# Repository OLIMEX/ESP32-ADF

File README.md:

# ESP32-ADF
ESP32 Audio Development Framework development board

[ESP32-ADF product page](https://www.olimex.com/Products/IoT/ESP32/ESP32-ADF/)

# ESP32-ADF board has these features:
- ESP32-WROVER-B module with 8MB PSRAM, 4MB Flash
- Stereo codec and Audio Amplifier 2x3W
- Stereo Microphones
- Audio out 3.5mm jack
- UEXT connector for sensors and LCDs
- Lipo battery charger
- USB connector and programmer
- Four touch buttons, 3 tactile buttons
- power supply Jack for +5V 1A

# License
- Hardware is with CERN OHL v1.2 license
- Software is with GPL3 license
- Documentation is with CC BY-SA 4.0 license

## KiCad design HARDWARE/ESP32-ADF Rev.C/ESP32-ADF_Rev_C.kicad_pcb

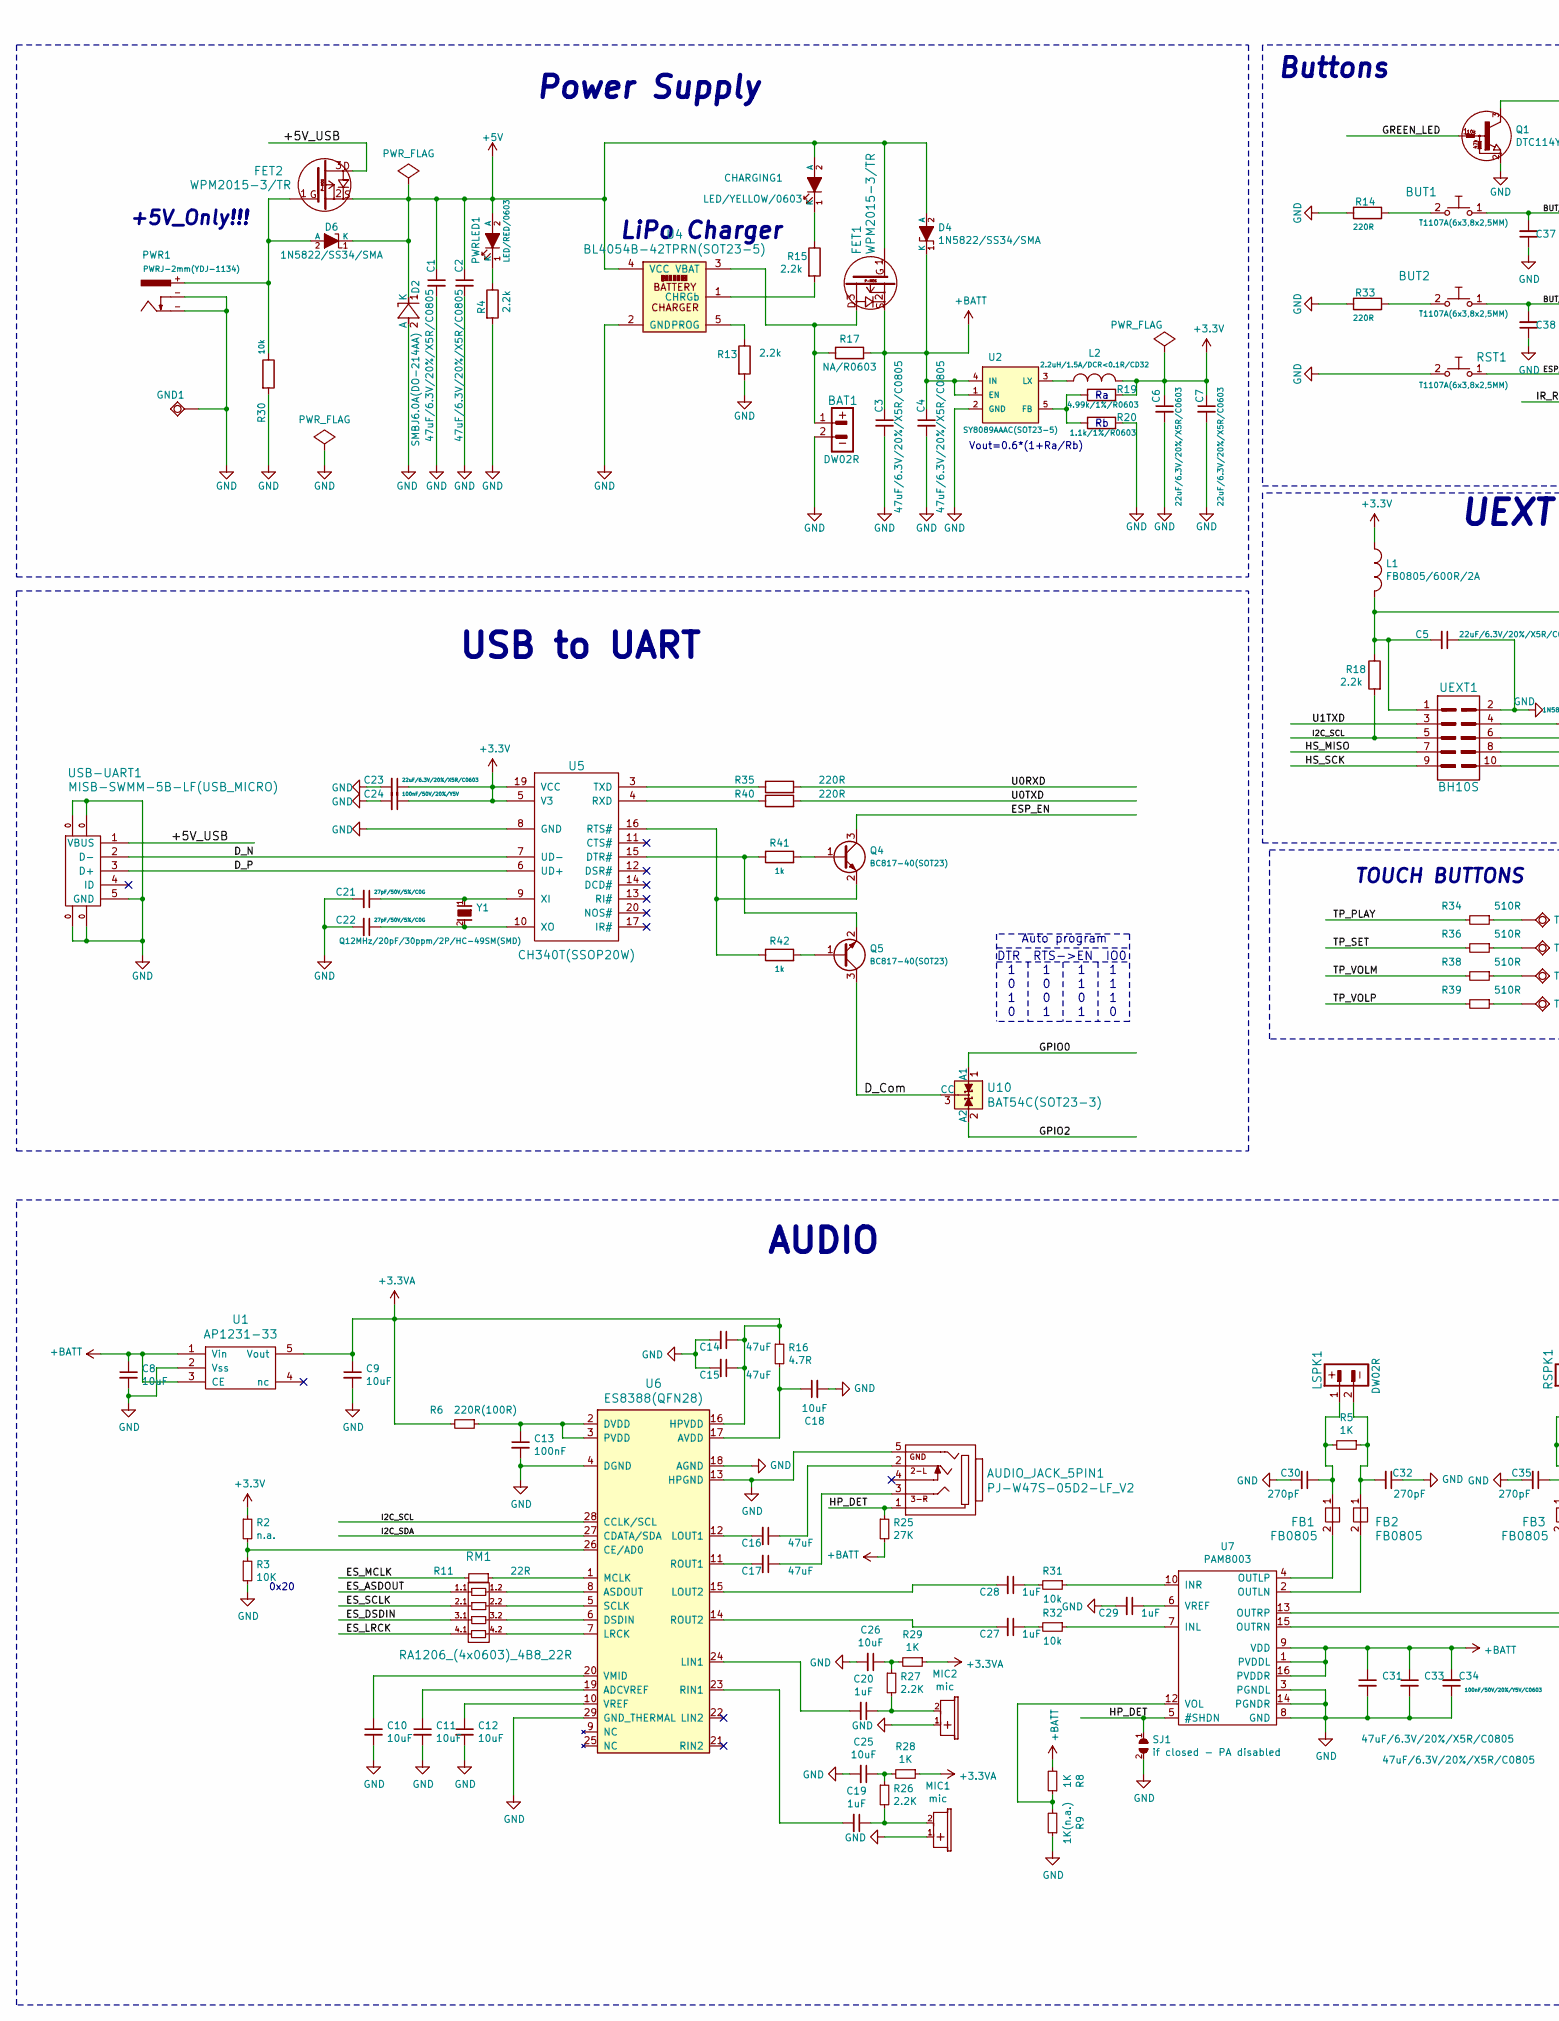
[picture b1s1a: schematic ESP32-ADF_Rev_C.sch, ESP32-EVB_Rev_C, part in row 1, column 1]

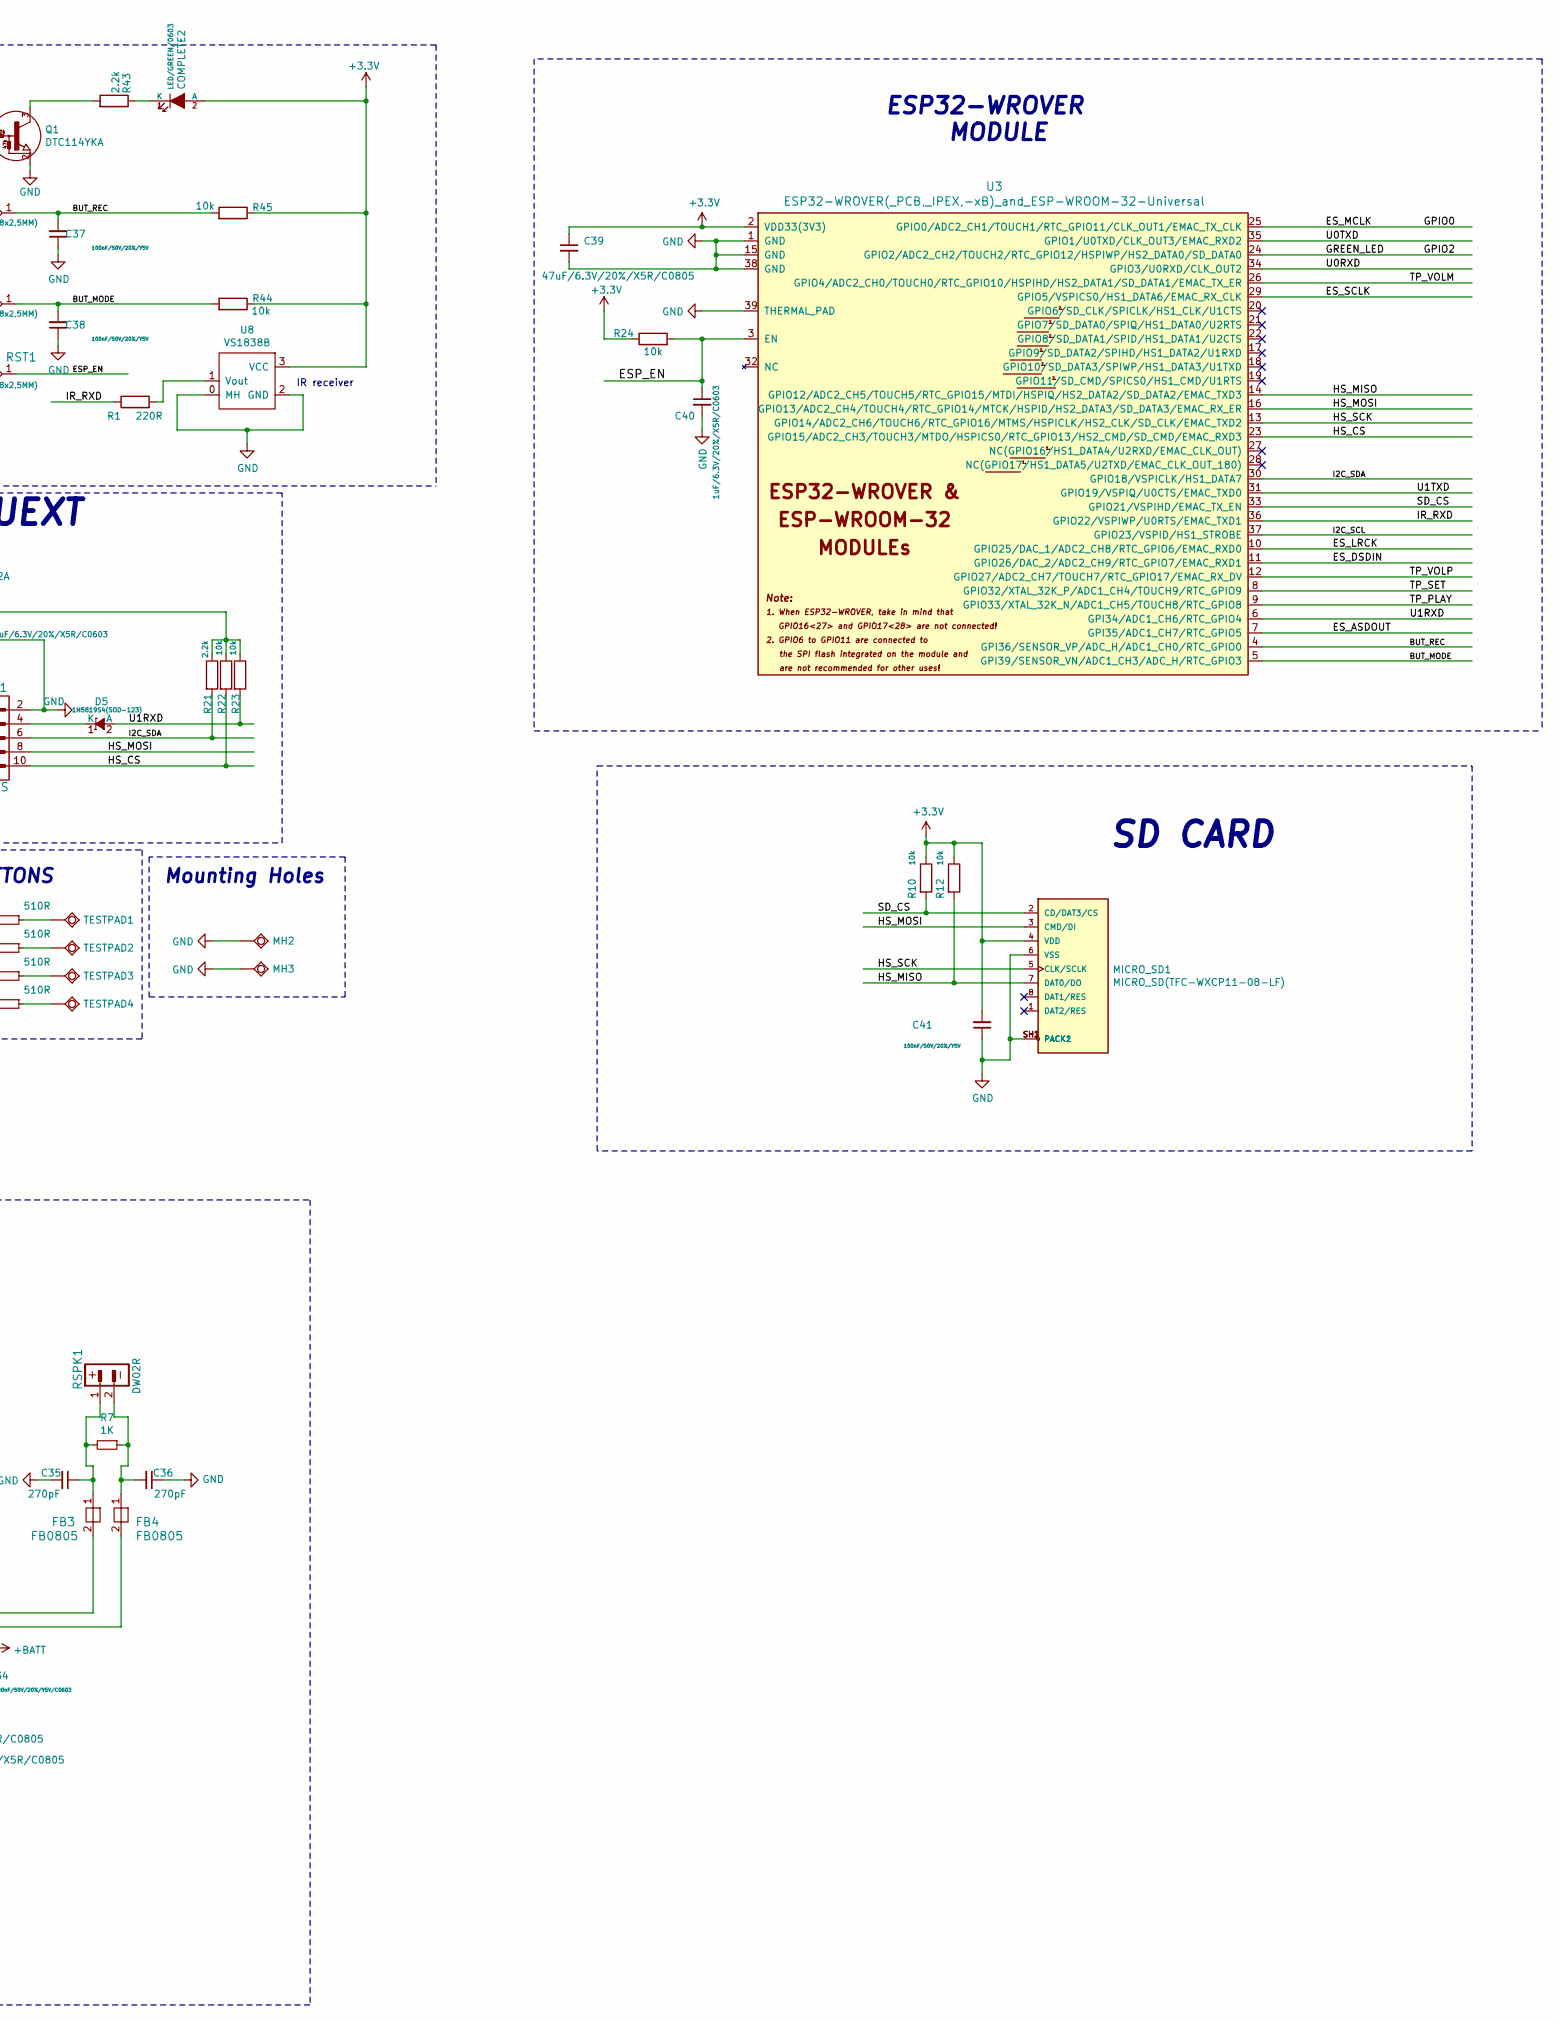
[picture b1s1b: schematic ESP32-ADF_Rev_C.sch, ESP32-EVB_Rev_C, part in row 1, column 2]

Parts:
AUDIO_JACK_5PIN1: PJ-W47S-05D2-LF_V2; PJ-W47S-05D2-LF_5PIN_V2
BAT1: DW02R; LIPO_BAT-CON2DW02R
BUT1, BUT2: T1107A(6x3,8x2,5MM)
C1, C2, C3, C4, C31, C33, C39: 47uF/6.3V/20%/X5R/C0805; C_0805_5MIL_DWS
C5, C6, C7, C23: 22uF/6.3V/20%/X5R/C0603; C_0603_5MIL_DWS
C8, C9, C10, C11, C12, C18, C25, C26: 10uF; C_0603_5MIL_DWS
C13: 100nF; C_0603_5MIL_DWS
C14, C15, C16, C17: 47uF; C_0805_5MIL_DWS
C19, C20, C27, C28, C29: 1uF; C_0603_5MIL_DWS
C21, C22: 27pF/50V/5%/C0G; C_0603_5MIL_DWS
C24: 100nF/50V/20%/Y5V; C_0603_5MIL_DWS
C30, C32, C35, C36: 270pF; C_0402_5MIL_DWS
C34: 100nF/50V/20%/Y5V/C0603; C_0402_5MIL_DWS
C37, C38, C41: 100nF/50V/20%/Y5V; C_0402_5MIL_DWS
C40: 1uF/6.3V/20%/X5R/C0603; C_0603_5MIL_DWS
CHARGING1: LED/YELLOW/0603; LED_0603_KA
COMPLETE2: LED/GREEN/0603; LED_0603_KA
D2: SMBJ6.0A(DO-214AA); DO214AA_1(K)-2(A)
D4, D6: 1N5822/SS34/SMA; SMA-KA
D5: 1N5819S4(SOD-123); SOD-123_1C-2A_KA
FB1, FB2, FB3, FB4: FB0805; L_0805_5MIL_DWS
FET1, FET2: WPM2015-3/TR; SOT23
GND1: TESTPAD; TESTPAD_40-ROUND
L1: FB0805/600R/2A; L_0805_5MIL_DWS
L2: 2.2uH/1.5A/DCR<0.1R/CD32; CD32
LSPK1: DW02R; LIPO_BAT-CON2DW02R
MH2, MH3: Mounting_hole_Shield_3.3mm
MIC1, MIC2: mic; MIC
MICRO_SD1: MICRO_SD(TFC-WXCP11-08-LF); TFC-WXCP11-08-LF
PWR1: PWRJ-2mm(YDJ-1134); PWRJ-2mm(YDJ-1136)
PWRLED1: LED/RED/0603; LED_0603_KA
Q1: DTC114YKA; SOT23
Q4, Q5: BC817-40(SOT23); SOT23
R1, R14, R33, R35, R40: 220R; R_0402_5MIL_DWS
R2: n.a.; R_0402_5MIL_DWS
R3: 10K; R_0402_5MIL_DWS
R4, R13, R15, R18, R21, R43: 2.2k; R_0402_5MIL_DWS
R5, R7, R8, R28, R29: 1K; R_0402_5MIL_DWS
R6: 220R(100R); R_0402_5MIL_DWS
R9: 1K(n.a.); R_0402_5MIL_DWS
R10, R12, R22, R23, R24, R30, R31, R32, R44, R45: 10k; R_0402_5MIL_DWS
R11: 22R; R_0402_5MIL_DWS
R16: 4.7R; R_0402_5MIL_DWS
R17: NA/R0603; R_0402_5MIL_DWS
R19: 4.99k/1%/R0603; R_0603_5MIL_DWS
R20: 1.1k/1%/R0603; R_0603_5MIL_DWS
R25: 27K; R_0402_5MIL_DWS
R26, R27: 2.2K; R_0402_5MIL_DWS
R34, R36, R38, R39: 510R; R_0402_5MIL_DWS
R41, R42: 1k; R_0402_5MIL_DWS
RM1: RA1206_(4x0603)_4B8_22R; RA1206_(4X0603)_4B8_mine_1.1
RSPK1: DW02R; LIPO_BAT-CON2DW02R
RST1: T1107A(6x3,8x2,5MM)
SJ1: if closed - PA disabled; SJ
TESTPAD1, TESTPAD2, TESTPAD3, TESTPAD4: TESTPAD; TP_SMD_10.00x5.00mm
U1: AP1231-33; SOT-23-5
U2: SY8089AAAC(SOT23-5); SOT-23-5
U3: ESP32-WROVER(_PCB,_IPEX,-xB)_and_ESP-WROOM-32-Uni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; ESP32-WROVER_MODULE_
U4: BL4054B-42TPRN(SOT23-5); SOT-23-5
U5: CH340T(SSOP20W); SSOP-20W
U6: ES8388(QFN28); QFN28_EP(29)_4.076x4.076x0.9mm_Pitch_0.45mm
U7: PAM8003; SO-16
U8: VS1838B; RPM7236-H8
U10: BAT54C(SOT23-3); SOT23
UEXT1: BH10S; GBH-254-SMT-10_Smaller
USB-UART1: MISB-SWMM-5B-LF(USB_MICRO); USB-MICRO_MISB-SWMM-5B_LF
Y1: Q12MHz/20pF/30ppm/2P/HC-49SM(SMD); TSX-3.2x2.5mm_GND(3)

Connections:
+3.3VA: C9.1, C14.1, C15.1, R6.2, R16.1, R28.1, R29.1, U1.5 (Vout), U6.16 (HPVDD)
+3V3: C6.1, C7.1, C23.1, C24.1, C39.1, C41.2, COMPLETE2.2 (A), L1.1, L2.2, MICRO_SD1.4 (VDD), R2.1, R10.1, R12.1, R19.2, R24.1, R44.1, R45.1, U3.2 (VDD33(3V3)), U5.5 (V3), U5.19 (VCC), U8.3 (VCC)
+5V: C1.1, C2.1, CHARGING1.2 (A), D2.1 (K), D4.2 (A), D6.1 (K), FET1.1, FET2.2, PWRLED1.2 (A), U4.4 (VCC)
+BATT: C3.1, C4.1, C8.1, C31.1, C33.1, C34.2, D4.1 (K), FET1.2, R8.2, R17.2, R25.2, U1.1 (Vin), U1.3 (CE), U2.1 (EN), U2.4 (IN), U7.1 (PVDDL), U7.9 (VDD), U7.16 (PVDDR)
/+5V_USB: FET2.3, USB-UART1.1 (VBUS)
/BUT_MODE: BUT2.1, C38.2, R44.2, U3.5 (GPI39/SENSOR_VN/ADC1_CH3/ADC_H/RTC_GPIO3)
/BUT_REC: BUT1.1, C37.2, R45.2, U3.4 (GPI36/SENSOR_VP/ADC_H/ADC1_CH0/RTC_GPIO0)
/D_Com: Q5.3 (C), U10.3 (CC)
/D_N: U5.7 (UD-), USB-UART1.2 (D-)
/D_P: U5.6 (UD+), USB-UART1.3 (D+)
/ESP_EN: C40.1, Q4.3 (C), R24.2, RST1.1, U3.3 (EN)
/ES_ASDOUT: RM1.1.1, U3.7 (GPI35/ADC1_CH7/RTC_GPIO5)
/ES_DSDIN: RM1.3.1, U3.11 (GPIO26/DAC_2/ADC2_CH9/RTC_GPIO7/EMAC_RX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)
/ES_LRCK: RM1.4.1, U3.10 (GPIO25/DAC_1/ADC2_CH8/RTC_GPIO6/EMAC_RX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)
/ES_MCLK: R11.2, U3.25 (GPIO0/ADC2_CH1/TOUCH1/RTC_GPIO11/CLK_OU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), U10.1 (A1)
/ES_SCLK: RM1.2.1, U3.29 (GPIO5/VSPICS0/HS1_DATA6/EMAC_RX_CLK)
/GPIO2: Q1.1 (B), U3.24 (GPIO2/ADC2_CH2/TOUCH2/RTC_GPIO12/HSPIWP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), U10.2 (A2)
/HP_DET: AUDIO_JACK_5PIN1.1, R25.1, SJ1.1, U7.5 (#SHDN)
/HS_CS: R22.2, U3.23 (GPIO15/ADC2_CH3/TOUCH3/MTDO/HSPICS0/RTC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), UEXT1.10
/HS_MISO: MICRO_SD1.7 (DAT0/DO), R12.2, U3.14 (GPIO12/ADC2_CH5/TOUCH5/RTC_GPIO15/MTDI/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), UEXT1.7
/HS_MOSI: MICRO_SD1.3 (CMD/DI), U3.16 (GPIO13/ADC2_CH4/TOUCH4/RTC_GPIO14/MTCK/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), UEXT1.8
/HS_SCK: MICRO_SD1.5 (CLK/SCLK), U3.13 (GPIO14/ADC2_CH6/TOUCH6/RTC_GPIO16/MTMS/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), UEXT1.9
/I2C_SCL: R18.2, U3.37 (GPIO23/VSPID/HS1_STROBE), U6.28 (CCLK/SCL), UEXT1.5
/I2C_SDA: R21.2, U3.30 (GPIO18/VSPICLK/HS1_DATA7), U6.27 (CDATA/SDA), UEXT1.6
/IR_RXD: R1.1, U3.36 (GPIO22/VSPIWP/U0RTS/EMAC_TXD1)
/SD_CS: MICRO_SD1.2 (CD/DAT3/CS), R10.2, U3.33 (GPIO21/VSPIHD/EMAC_TX_EN)
/TP_PLAY: R34.2, U3.9 (GPIO33/XTAL_32K_N/ADC1_CH5/TOUCH8/RTC_G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)
/TP_SET: R36.2, U3.8 (GPIO32/XTAL_32K_P/ADC1_CH4/TOUCH9/RTC_G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)
/TP_VOLM: R38.2, U3.26 (GPIO4/ADC2_CH0/TOUCH0/RTC_GPIO10/HSPIHD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)
/TP_VOLP: R39.2, U3.12 (GPIO27/ADC2_CH7/TOUCH7/RTC_GPIO17/EMAC_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)
/U0RXD: R35.2, U3.34 (GPIO3/U0RXD/CLK_OUT2)
/U0TXD: R40.2, U3.35 (GPIO1/U0TXD/CLK_OUT3/EMAC_RXD2)
/U1RXD: D5.2 (A), R23.2, U3.6 (GPI34/ADC1_CH6/RTC_GPIO4)
/U1TXD: U3.31 (GPIO19/VSPIQ/U0CTS/EMAC_TXD0), UEXT1.3
GND: AUDIO_JACK_5PIN1.5, BAT1.2, C1.2, C2.2, C3.2, C4.2, C5.1, C6.2, C7.2, C8.2, C9.2, C10.2, C11.2, C12.2, C13.2, C14.2, C15.2, C18.2, C21.2, C22.2, C23.2, C24.2, C25.2, C26.2, C29.2, C30.2, C31.2, C32.1, C33.2, C34.1, C35.2, C36.1, C37.1, C38.1, C39.2, C40.2, C41.1, D2.2 (A), GND1.1, MH2.GND1, MH3.GND1, MIC1.1 (PLUS), MIC2.1 (PLUS), MICRO_SD1.6 (VSS), MICRO_SD1.SH1 (PACK1), MICRO_SD1.SH2 (PACK2), PWR1.-, Q1.2 (E), R3.2, R4.2, R9.1, R13.2, R14.2, R20.2, R30.2, R33.2, RST1.2, SJ1.2, U1.2 (Vss), U2.2 (GND), U3.1 (GND), U3.15 (GND), U3.38 (GND), U3.39 (THERMAL_PAD), U4.2 (GND), U5.8 (GND), U6.4 (DGND), U6.13 (HPGND), U6.18 (AGND), U6.29 (GND_THERMAL), U7.3 (PGNDL), U7.8 (GND), U7.14 (PGNDR), U8.0 (MH), U8.2 (GND), UEXT1.2, USB-UART1.0, USB-UART1.5 (GND); also elsewhere on the board
unnamed: AUDIO_JACK_5PIN1.2, C16.1
unnamed: AUDIO_JACK_5PIN1.3, C17.1
unnamed: BAT1.1, FET1.3, R17.1, U4.3 (VBAT)
unnamed: BUT1.2, R14.1
unnamed: BUT2.2, R33.1
unnamed: C5.2, L1.2, R18.1, R21.1, R22.1, R23.1, UEXT1.1
unnamed: C10.1, U6.20 (VMID)
unnamed: C11.1, U6.19 (ADCVREF)
unnamed: C12.1, U6.10 (VREF)
unnamed: C13.1, R6.1, U6.2 (DVDD), U6.3 (PVDD)
unnamed: C16.2, U6.12 (LOUT1)
unnamed: C17.2, U6.11 (ROUT1)
unnamed: C18.1, R16.2, U6.17 (AVDD)
unnamed: C19.1, MIC1.2 (MINUS), R26.2
unnamed: C19.2, U6.23 (RIN1)
unnamed: C20.1, MIC2.2 (MINUS), R27.2
unnamed: C20.2, U6.24 (LIN1)
unnamed: C21.1, U5.9 (XI), Y1.1
unnamed: C22.1, U5.10 (XO), Y1.2
unnamed: C25.1, R26.1, R28.2
unnamed: C26.1, R27.1, R29.2
unnamed: C27.1, R31.2
unnamed: C27.2, U6.14 (ROUT2)
unnamed: C28.1, R32.2
unnamed: C28.2, U6.15 (LOUT2)
unnamed: C29.1, U7.6 (VREF)
unnamed: C30.1, FB1.1, LSPK1.1, R5.2
unnamed: C32.2, FB2.1, LSPK1.2, R5.1
unnamed: C35.1, FB3.1, R7.2, RSPK1.1
unnamed: C36.2, FB4.1, R7.1, RSPK1.2
unnamed: CHARGING1.1 (K), R15.1
unnamed: COMPLETE2.1 (K), R43.1
unnamed: D5.1 (K), UEXT1.4
unnamed: D6.2 (A), FET2.1, PWR1.+, R30.1
unnamed: FB1.2, U7.4 (OUTLP)
unnamed: FB2.2, U7.2 (OUTLN)
unnamed: FB3.2, U7.13 (OUTRP)
unnamed: FB4.2, U7.15 (OUTRN)
unnamed: L2.1, U2.3 (LX)
unnamed: PWRLED1.1 (K), R4.1
unnamed: Q1.3 (C), R43.2
unnamed: Q4.1 (B), R41.2
unnamed: Q4.2 (E), R42.1, U5.16 (RTS#)
unnamed: Q5.1 (B), R42.2
unnamed: Q5.2 (E), R41.1, U5.15 (DTR#)
unnamed: R1.2, U8.1 (Vout)
unnamed: R2.2, R3.1, U6.26 (CE/AD0)
unnamed: R8.1, R9.2, U7.12 (VOL)
unnamed: R11.1, U6.1 (MCLK)
unnamed: R13.1, U4.5 (PROG)
unnamed: R15.2, U4.1 (CHRGb)
unnamed: R19.1, R20.1, U2.5 (FB)
unnamed: R31.1, U7.7 (INL)
unnamed: R32.1, U7.10 (INR)
unnamed: R34.1, TESTPAD1.1
unnamed: R35.1, U5.3 (TXD)
unnamed: R36.1, TESTPAD2.1
unnamed: R38.1, TESTPAD3.1
unnamed: R39.1, TESTPAD4.1
unnamed: R40.1, U5.4 (RXD)
unnamed: RM1.1.2, U6.8 (ASDOUT)
unnamed: RM1.2.2, U6.5 (SCLK)
unnamed: RM1.3.2, U6.6 (DSDIN)
unnamed: RM1.4.2, U6.7 (LRCK)

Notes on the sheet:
Vout=0.6*(1+Ra/Rb)
Power Supply
Buttons
UEXT
ESP32-WROVER MODULE
Mounting Holes
LiPo Charger
+5V_Only!!!
Auto program
DTR RTS->EN IO0
USB to UART
0x20
AUDIO
TOUCH BUTTONS
IR receiver
SD CARD

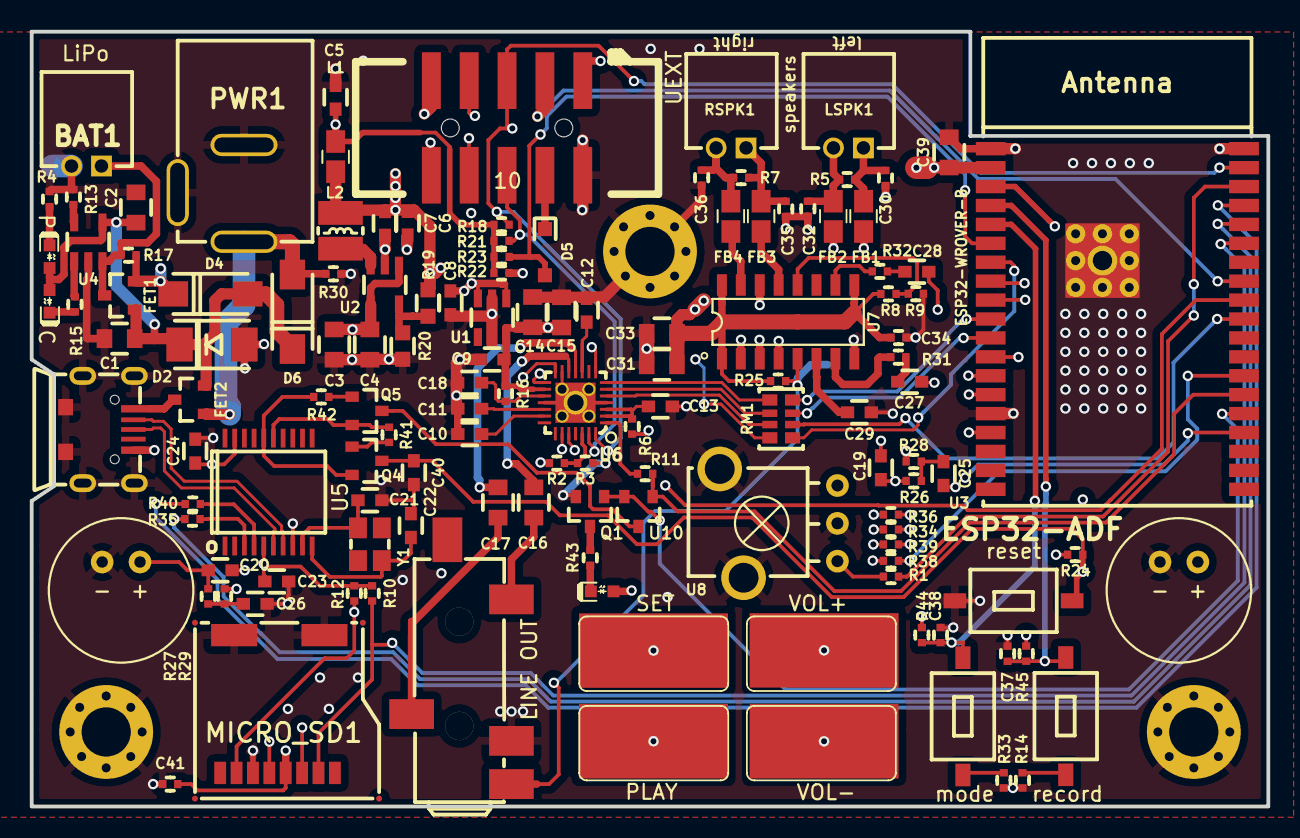
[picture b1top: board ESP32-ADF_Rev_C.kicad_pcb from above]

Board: 4 copper layers, 83.0 x 52.0 mm, 135 parts (1 on the bottom side), 99 nets.

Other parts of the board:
MH3#2: Mounting_hole_Shield_3.3mm

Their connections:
GND: MH3#2.GND1; also elsewhere on the board

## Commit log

2019-07-18 initial upload
2019-07-18 add pdf schematic
2019-07-29 add software demo
2019-07-29 Google Voice assistant, Google Dialogflow, Amazon Alexa
2019-07-30 added MOD-LCD2.8RTP display
2019-08-01 added mod-lcd2.8rtp config
2020-11-23 Update
    Revision C files
2020-11-23 Update
    added change log
2021-10-04 Update
    Added PDF export
